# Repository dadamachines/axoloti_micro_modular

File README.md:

# axoloti_micro_modular
a open hardware micro modular based on the awesome axoloti core board

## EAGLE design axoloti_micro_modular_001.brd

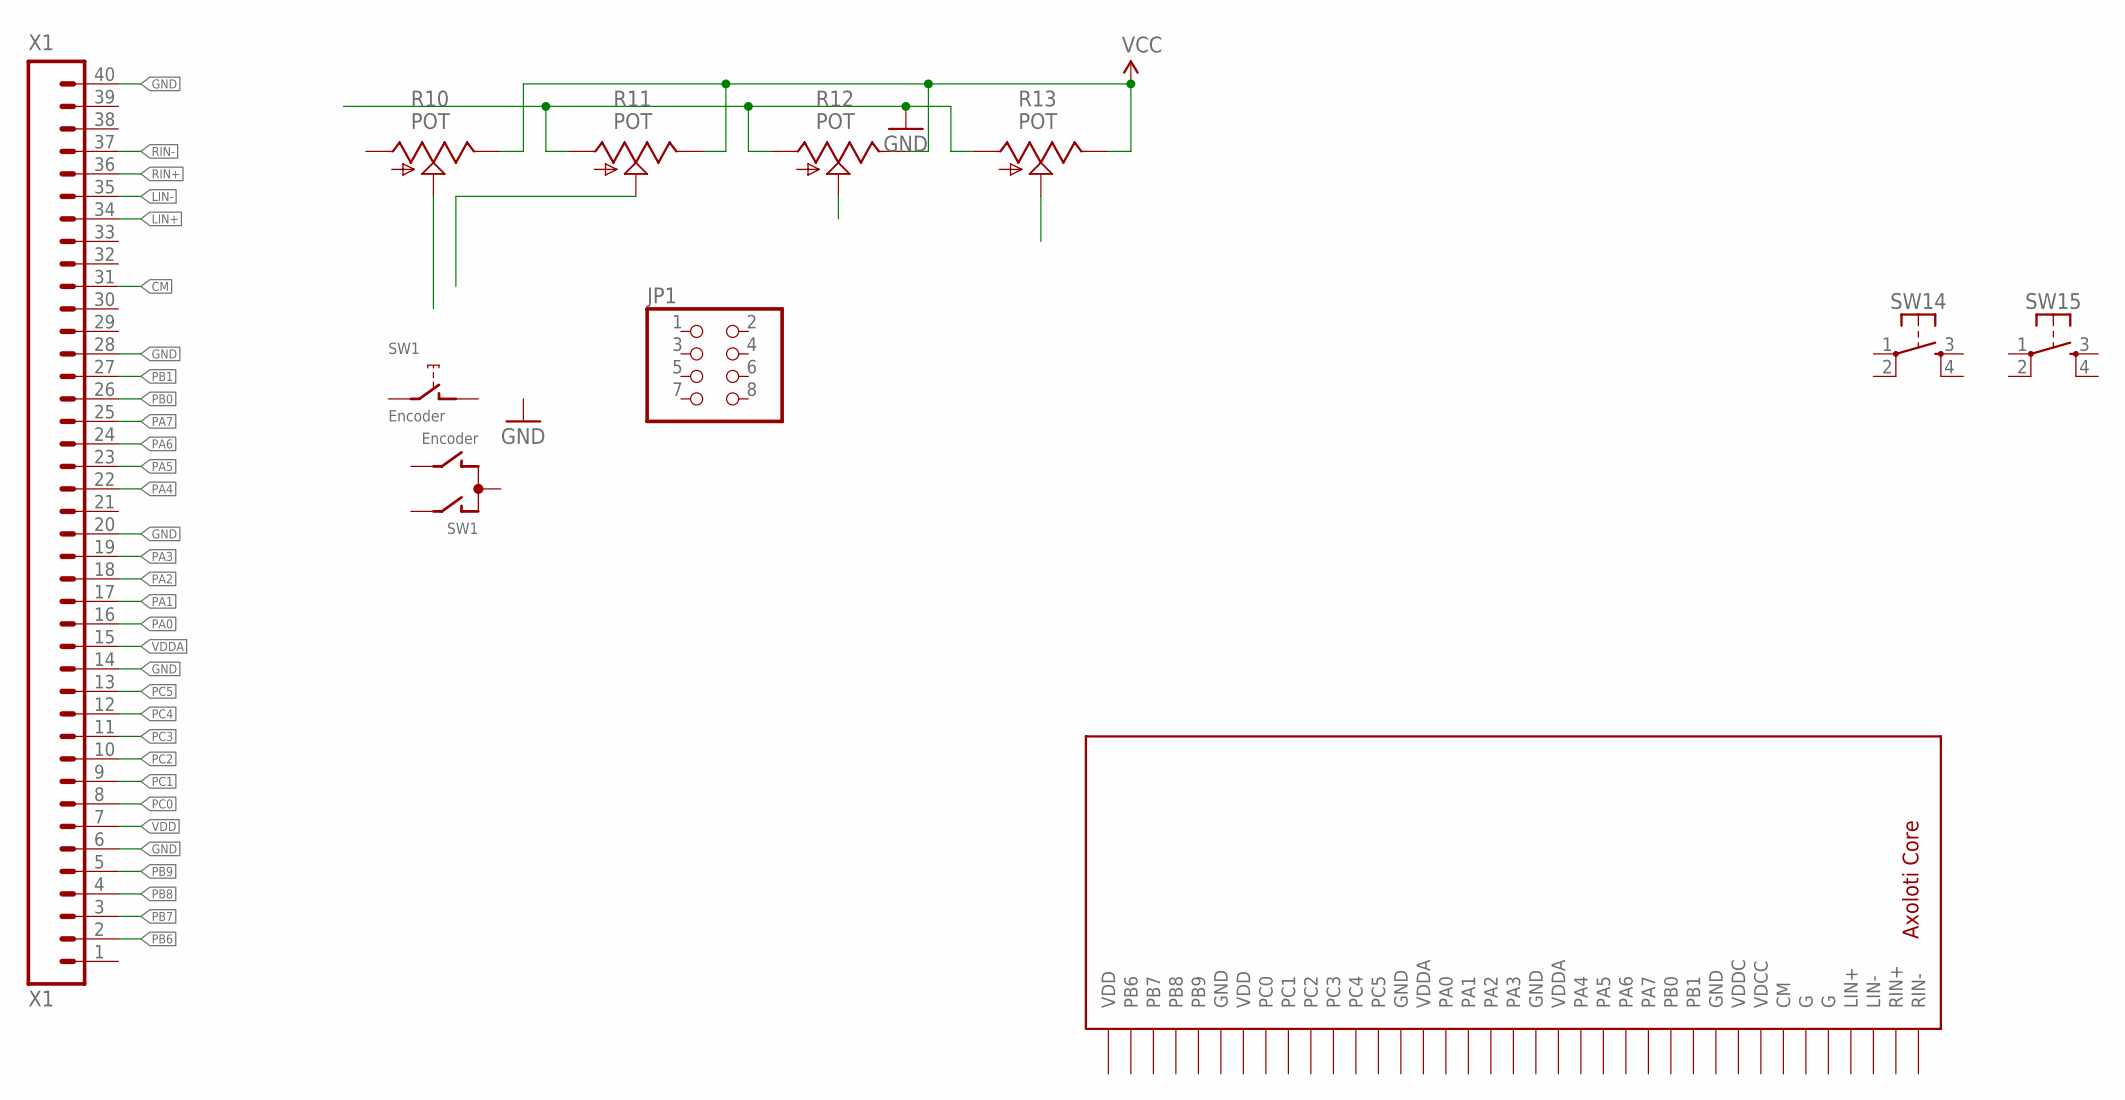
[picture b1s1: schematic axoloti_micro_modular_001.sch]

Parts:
JP1: PINHD-2X4; 2X04
R10, R11, R12, R13: POT; ALPS_POT_SFE
SW1: Encoder; ALPS_EC12E_SW
SW14, SW15: SW-TACTILE-6X6; SW6X6
U$1: AXOLOTI_SHIELD_CUTOUT
X1: X1; 1X40

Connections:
CM: X1.31
GND: R11.P$3 (A), R12.P$3 (A), R13.P$3 (A), X1.6, X1.14, X1.20, X1.28, X1.40
LIN+: X1.34
LIN-: X1.35
PA0: X1.16
PA1: X1.17
PA2: X1.18
PA3: X1.19
PA4: X1.22
PA5: X1.23
PA6: X1.24
PA7: X1.25
PB0: X1.26
PB1: X1.27
PB6: X1.2
PB7: X1.3
PB8: X1.4
PB9: X1.5
PC0: X1.8
PC1: X1.9
PC2: X1.10
PC3: X1.11
PC4: X1.12
PC5: X1.13
RIN+: X1.36
RIN-: X1.37
VCC: R10.P$1 (E), R11.P$1 (E), R12.P$1 (E), R13.P$1 (E)
VDD: X1.7
VDDA: X1.15

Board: 2 copper layers, 13 parts (0 on the bottom side), 2 nets, no tracks yet.

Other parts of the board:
H1, H4, H7: MOUNT-HOLE3.0; 3,0

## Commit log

2016-01-13 commit the first sketch and work from there

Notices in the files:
parts and their libraries:
SparkFun-Connectors: Licensing: CC v3.0 Share-Alike You are welcome to use this library for commercial purposes.
